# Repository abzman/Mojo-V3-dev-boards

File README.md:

# Mojo-V3-dev-boards
boards to use my mojo v3 as a development system for other FPGA projects

5v levelshifter bard can be purchased from PCBway here: https://www.pcbway.com/project/shareproject/64_bit_bidirectional_5v_shield_for_mojoV3_945b0e26.html

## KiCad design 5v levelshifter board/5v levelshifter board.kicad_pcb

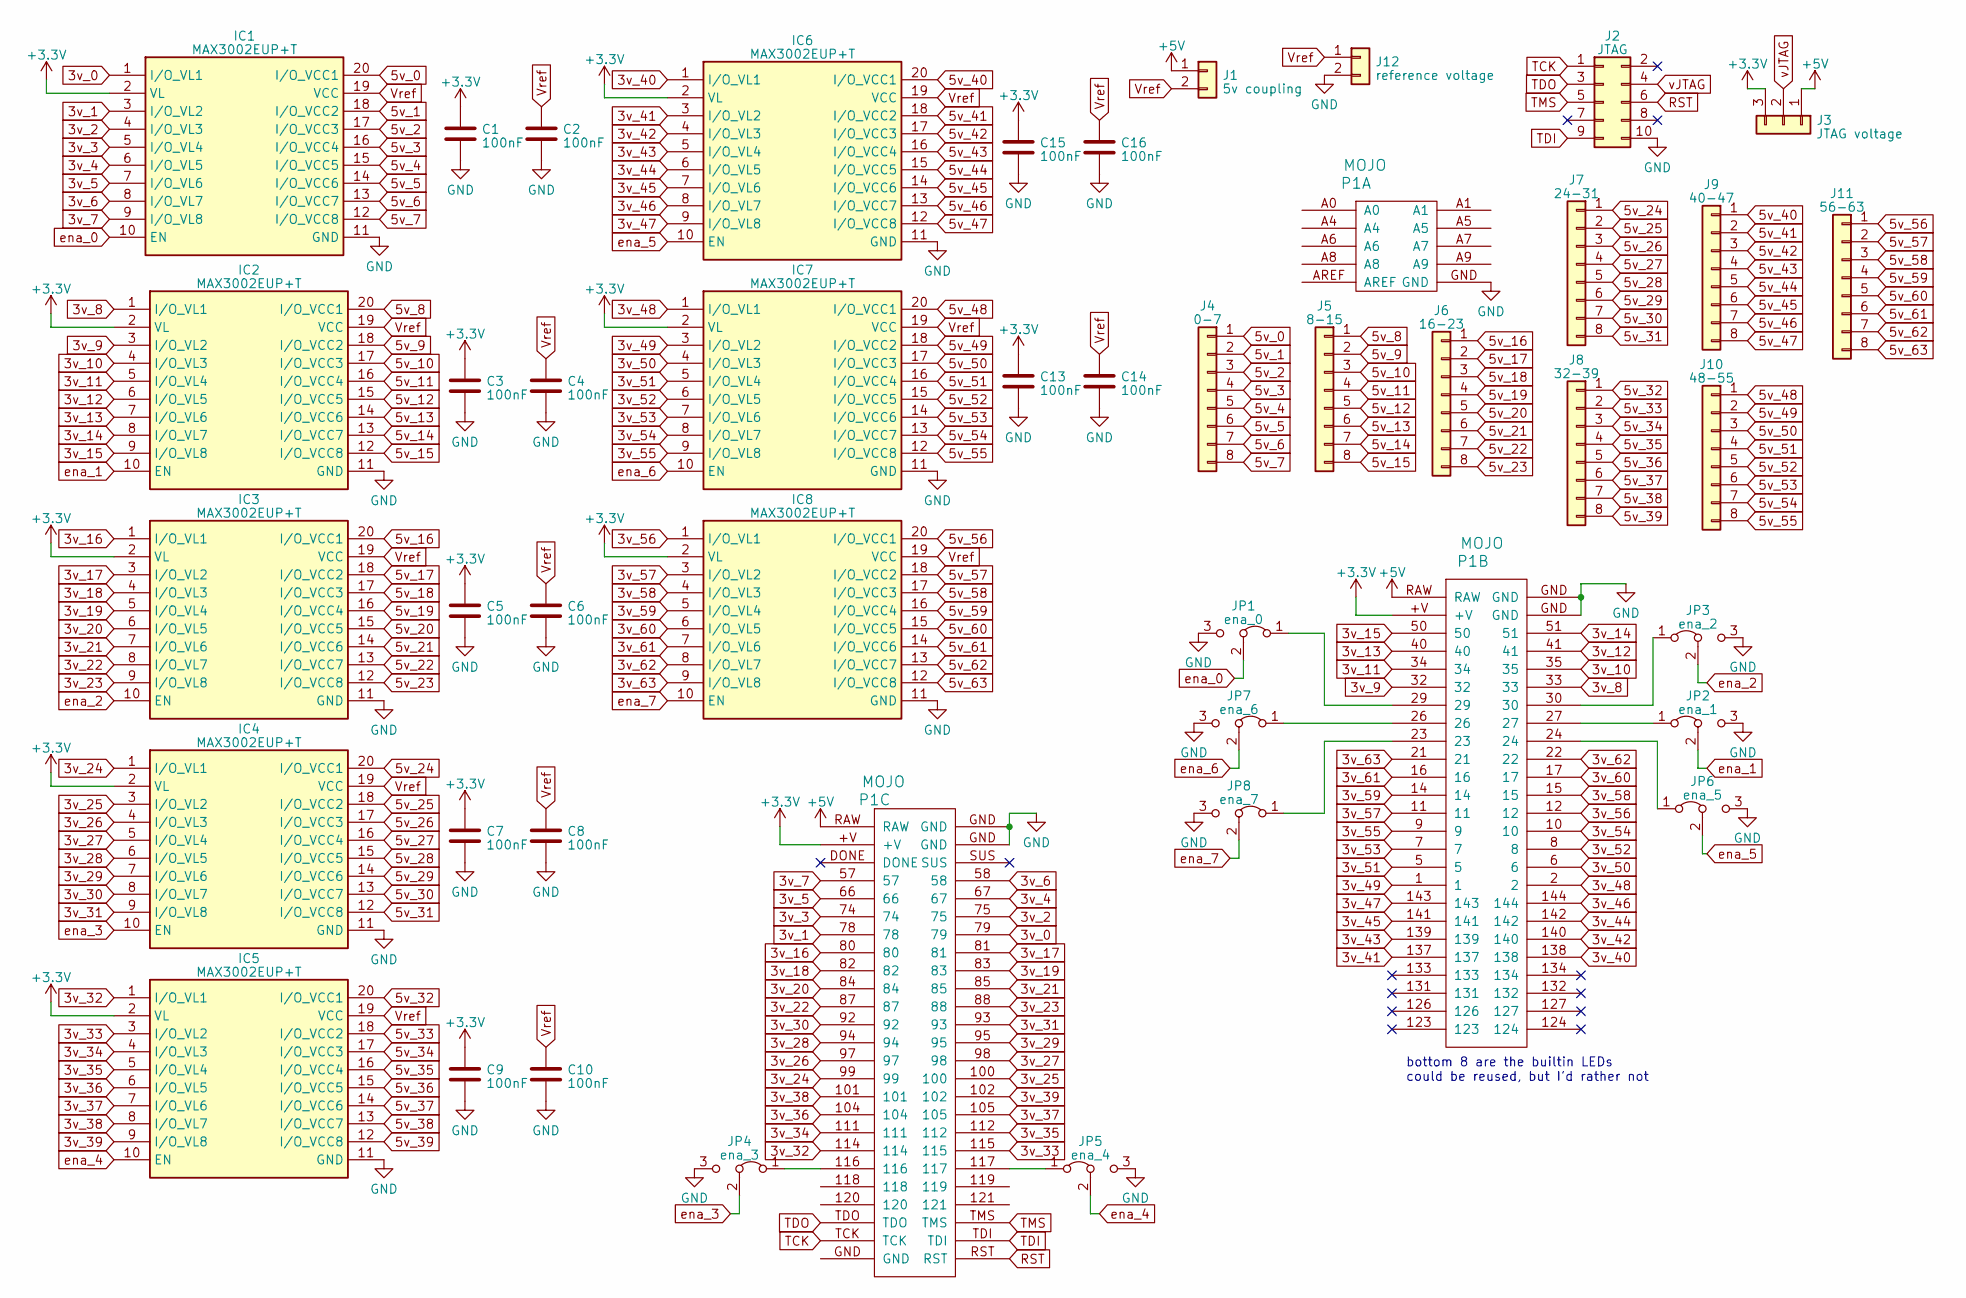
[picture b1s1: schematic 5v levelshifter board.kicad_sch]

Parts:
C1, C2, C3, C4, C5, C6, C7, C8, C9, C10, C13, C14, C15, C16: 100nF; C_0603_1608Metric
IC1, IC2, IC3, IC4, IC5, IC6, IC7, IC8: MAX3002EUP+T; SOP65P640X110-20N; Mouser Part Number 700-MAX3002EUPT
J1: 5v coupling; PinHeader_2x01_P2.54mm_Vertical
J2: JTAG; PinHeader_2x05_P2.54mm_Vertical
J3: JTAG voltage; PinHeader_1x03_P2.54mm_Vertical
J4: 0-7; PinHeader_1x08_P2.54mm_Vertical
J5: 8-15; PinHeader_1x08_P2.54mm_Vertical
J6: 16-23; PinHeader_1x08_P2.54mm_Vertical
J7: 24-31; PinHeader_1x08_P2.54mm_Vertical
J8: 32-39; PinHeader_1x08_P2.54mm_Vertical
J9: 40-47; PinHeader_1x08_P2.54mm_Vertical
J10: 48-55; PinHeader_1x08_P2.54mm_Vertical
J11: 56-63; PinHeader_1x08_P2.54mm_Vertical
J12: reference voltage; PinHeader_2x01_P2.54mm_Vertical
JP1: ena_0; SolderJumper-3_P1.3mm_Bridged12_RoundedPad1.0x1.5mm_NumberL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
JP2: ena_1; SolderJumper-3_P1.3mm_Bridged12_RoundedPad1.0x1.5mm_NumberL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
JP3: ena_2; SolderJumper-3_P1.3mm_Bridged12_RoundedPad1.0x1.5mm_NumberL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
JP4: ena_3; SolderJumper-3_P1.3mm_Bridged12_RoundedPad1.0x1.5mm_NumberL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
JP5: ena_4; SolderJumper-3_P1.3mm_Bridged12_RoundedPad1.0x1.5mm_NumberL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
JP6: ena_5; SolderJumper-3_P1.3mm_Bridged12_RoundedPad1.0x1.5mm_NumberL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
JP7: ena_6; SolderJumper-3_P1.3mm_Bridged12_RoundedPad1.0x1.5mm_NumberL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
JP8: ena_7; SolderJumper-3_P1.3mm_Bridged12_RoundedPad1.0x1.5mm_NumberL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
P1: MOJO; Mojo

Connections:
3v_0: IC1.1 (I/O_VL1), P1.79
3v_1: IC1.3 (I/O_VL2), P1.78
3v_2: IC1.4 (I/O_VL3), P1.75
3v_3: IC1.5 (I/O_VL4), P1.74
3v_4: IC1.6 (I/O_VL5), P1.67
3v_5: IC1.7 (I/O_VL6), P1.66
3v_6: IC1.8 (I/O_VL7), P1.58
3v_7: IC1.9 (I/O_VL8), P1.57
3v_8: IC2.1 (I/O_VL1), P1.33
3v_9: IC2.3 (I/O_VL2), P1.32
3v_10: IC2.4 (I/O_VL3), P1.35
3v_11: IC2.5 (I/O_VL4), P1.34
3v_12: IC2.6 (I/O_VL5), P1.41
3v_13: IC2.7 (I/O_VL6), P1.40
3v_14: IC2.8 (I/O_VL7), P1.51
3v_15: IC2.9 (I/O_VL8), P1.50
3v_16: IC3.1 (I/O_VL1), P1.80
3v_17: IC3.3 (I/O_VL2), P1.81
3v_18: IC3.4 (I/O_VL3), P1.82
3v_19: IC3.5 (I/O_VL4), P1.83
3v_20: IC3.6 (I/O_VL5), P1.84
3v_21: IC3.7 (I/O_VL6), P1.85
3v_22: IC3.8 (I/O_VL7), P1.87
3v_23: IC3.9 (I/O_VL8), P1.88
3v_24: IC4.1 (I/O_VL1), P1.99
3v_25: IC4.3 (I/O_VL2), P1.100
3v_26: IC4.4 (I/O_VL3), P1.97
3v_27: IC4.5 (I/O_VL4), P1.98
3v_28: IC4.6 (I/O_VL5), P1.94
3v_29: IC4.7 (I/O_VL6), P1.95
3v_30: IC4.8 (I/O_VL7), P1.92
3v_31: IC4.9 (I/O_VL8), P1.93
3v_32: IC5.1 (I/O_VL1), P1.114
3v_33: IC5.3 (I/O_VL2), P1.115
3v_34: IC5.4 (I/O_VL3), P1.111
3v_35: IC5.5 (I/O_VL4), P1.112
3v_36: IC5.6 (I/O_VL5), P1.104
3v_37: IC5.7 (I/O_VL6), P1.105
3v_38: IC5.8 (I/O_VL7), P1.101
3v_39: IC5.9 (I/O_VL8), P1.102
3v_40: IC6.1 (I/O_VL1), P1.138
3v_41: IC6.3 (I/O_VL2), P1.137
3v_42: IC6.4 (I/O_VL3), P1.140
3v_43: IC6.5 (I/O_VL4), P1.139
3v_44: IC6.6 (I/O_VL5), P1.142
3v_45: IC6.7 (I/O_VL6), P1.141
3v_46: IC6.8 (I/O_VL7), P1.144
3v_47: IC6.9 (I/O_VL8), P1.143
3v_48: IC7.1 (I/O_VL1), P1.2
3v_49: IC7.3 (I/O_VL2), P1.1
3v_50: IC7.4 (I/O_VL3), P1.6
3v_51: IC7.5 (I/O_VL4), P1.5
3v_52: IC7.6 (I/O_VL5), P1.8
3v_53: IC7.7 (I/O_VL6), P1.7
3v_54: IC7.8 (I/O_VL7), P1.10
3v_55: IC7.9 (I/O_VL8), P1.9
3v_56: IC8.1 (I/O_VL1), P1.12
3v_57: IC8.3 (I/O_VL2), P1.11
3v_58: IC8.4 (I/O_VL3), P1.15
3v_59: IC8.5 (I/O_VL4), P1.14
3v_60: IC8.6 (I/O_VL5), P1.17
3v_61: IC8.7 (I/O_VL6), P1.16
3v_62: IC8.8 (I/O_VL7), P1.22
3v_63: IC8.9 (I/O_VL8), P1.21
5v_0: IC1.20 (I/O_VCC1), J4.1
5v_1: IC1.18 (I/O_VCC2), J4.2
5v_2: IC1.17 (I/O_VCC3), J4.3
5v_3: IC1.16 (I/O_VCC4), J4.4
5v_4: IC1.15 (I/O_VCC5), J4.5
5v_5: IC1.14 (I/O_VCC6), J4.6
5v_6: IC1.13 (I/O_VCC7), J4.7
5v_7: IC1.12 (I/O_VCC8), J4.8
5v_8: IC2.20 (I/O_VCC1), J5.1
5v_9: IC2.18 (I/O_VCC2), J5.2
5v_10: IC2.17 (I/O_VCC3), J5.3
5v_11: IC2.16 (I/O_VCC4), J5.4
5v_12: IC2.15 (I/O_VCC5), J5.5
5v_13: IC2.14 (I/O_VCC6), J5.6
5v_14: IC2.13 (I/O_VCC7), J5.7
5v_15: IC2.12 (I/O_VCC8), J5.8
5v_16: IC3.20 (I/O_VCC1), J6.1
5v_17: IC3.18 (I/O_VCC2), J6.2
5v_18: IC3.17 (I/O_VCC3), J6.3
5v_19: IC3.16 (I/O_VCC4), J6.4
5v_20: IC3.15 (I/O_VCC5), J6.5
5v_21: IC3.14 (I/O_VCC6), J6.6
5v_22: IC3.13 (I/O_VCC7), J6.7
5v_23: IC3.12 (I/O_VCC8), J6.8
5v_24: IC4.20 (I/O_VCC1), J7.1
5v_25: IC4.18 (I/O_VCC2), J7.2
5v_26: IC4.17 (I/O_VCC3), J7.3
5v_27: IC4.16 (I/O_VCC4), J7.4
5v_28: IC4.15 (I/O_VCC5), J7.5
5v_29: IC4.14 (I/O_VCC6), J7.6
5v_30: IC4.13 (I/O_VCC7), J7.7
5v_31: IC4.12 (I/O_VCC8), J7.8
5v_32: IC5.20 (I/O_VCC1), J8.1
5v_33: IC5.18 (I/O_VCC2), J8.2
5v_34: IC5.17 (I/O_VCC3), J8.3
5v_35: IC5.16 (I/O_VCC4), J8.4
5v_36: IC5.15 (I/O_VCC5), J8.5
5v_37: IC5.14 (I/O_VCC6), J8.6
5v_38: IC5.13 (I/O_VCC7), J8.7
5v_39: IC5.12 (I/O_VCC8), J8.8
5v_40: IC6.20 (I/O_VCC1), J9.1
5v_41: IC6.18 (I/O_VCC2), J9.2
5v_42: IC6.17 (I/O_VCC3), J9.3
5v_43: IC6.16 (I/O_VCC4), J9.4
5v_44: IC6.15 (I/O_VCC5), J9.5
5v_45: IC6.14 (I/O_VCC6), J9.6
5v_46: IC6.13 (I/O_VCC7), J9.7
5v_47: IC6.12 (I/O_VCC8), J9.8
5v_48: IC7.20 (I/O_VCC1), J10.1
5v_49: IC7.18 (I/O_VCC2), J10.2
5v_50: IC7.17 (I/O_VCC3), J10.3
5v_51: IC7.16 (I/O_VCC4), J10.4
5v_52: IC7.15 (I/O_VCC5), J10.5
5v_53: IC7.14 (I/O_VCC6), J10.6
5v_54: IC7.13 (I/O_VCC7), J10.7
5v_55: IC7.12 (I/O_VCC8), J10.8
5v_56: IC8.20 (I/O_VCC1), J11.1
5v_57: IC8.18 (I/O_VCC2), J11.2
5v_58: IC8.17 (I/O_VCC3), J11.3
5v_59: IC8.16 (I/O_VCC4), J11.4
5v_60: IC8.15 (I/O_VCC5), J11.5
5v_61: IC8.14 (I/O_VCC6), J11.6
5v_62: IC8.13 (I/O_VCC7), J11.7
5v_63: IC8.12 (I/O_VCC8), J11.8
+3.3V: C1.1, C3.1, C5.1, C7.1, C9.1, C13.1, C15.1, IC1.2 (VL), IC2.2 (VL), IC3.2 (VL), IC4.2 (VL), IC5.2 (VL), IC6.2 (VL), IC7.2 (VL), IC8.2 (VL), J3.3, P1.+V
+5V: J1.1, J3.1, P1.RAW
GND: C1.2, C2.2, C3.2, C4.2, C5.2, C6.2, C7.2, C8.2, C9.2, C10.2, C13.2, C14.2, C15.2, C16.2, IC1.11 (GND), IC2.11 (GND), IC3.11 (GND), IC4.11 (GND), IC5.11 (GND), IC6.11 (GND), IC7.11 (GND), IC8.11 (GND), J2.10, J12.2, JP1.3 (B), JP2.3 (B), JP3.3 (B), JP4.3 (B), JP5.3 (B), JP6.3 (B), JP7.3 (B), JP8.3 (B), P1.GND
unnamed: JP1.1 (A), P1.29
unnamed: JP2.1 (A), P1.27
unnamed: JP3.1 (A), P1.30
unnamed: JP4.1 (A), P1.116
unnamed: JP5.1 (A), P1.117
unnamed: JP6.1 (A), P1.24
unnamed: JP7.1 (A), P1.26
unnamed: JP8.1 (A), P1.23
RST: J2.6, P1.RST
TCK: J2.1, P1.TCK
TDI: J2.9, P1.TDI
TDO: J2.3, P1.TDO
TMS: J2.5, P1.TMS
Vref: C2.1, C4.1, C6.1, C8.1, C10.1, C14.1, C16.1, IC1.19 (VCC), IC2.19 (VCC), IC3.19 (VCC), IC4.19 (VCC), IC5.19 (VCC), IC6.19 (VCC), IC7.19 (VCC), IC8.19 (VCC), J1.2, J12.1
ena_0: IC1.10 (EN), JP1.2 (C)
ena_1: IC2.10 (EN), JP2.2 (C)
ena_2: IC3.10 (EN), JP3.2 (C)
ena_3: IC4.10 (EN), JP4.2 (C)
ena_4: IC5.10 (EN), JP5.2 (C)
ena_5: IC6.10 (EN), JP6.2 (C)
ena_6: IC7.10 (EN), JP7.2 (C)
ena_7: IC8.10 (EN), JP8.2 (C)
vJTAG: J2.4, J3.2

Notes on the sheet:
bottom 8 are the builtin LEDs could be reused, but I'd rather not

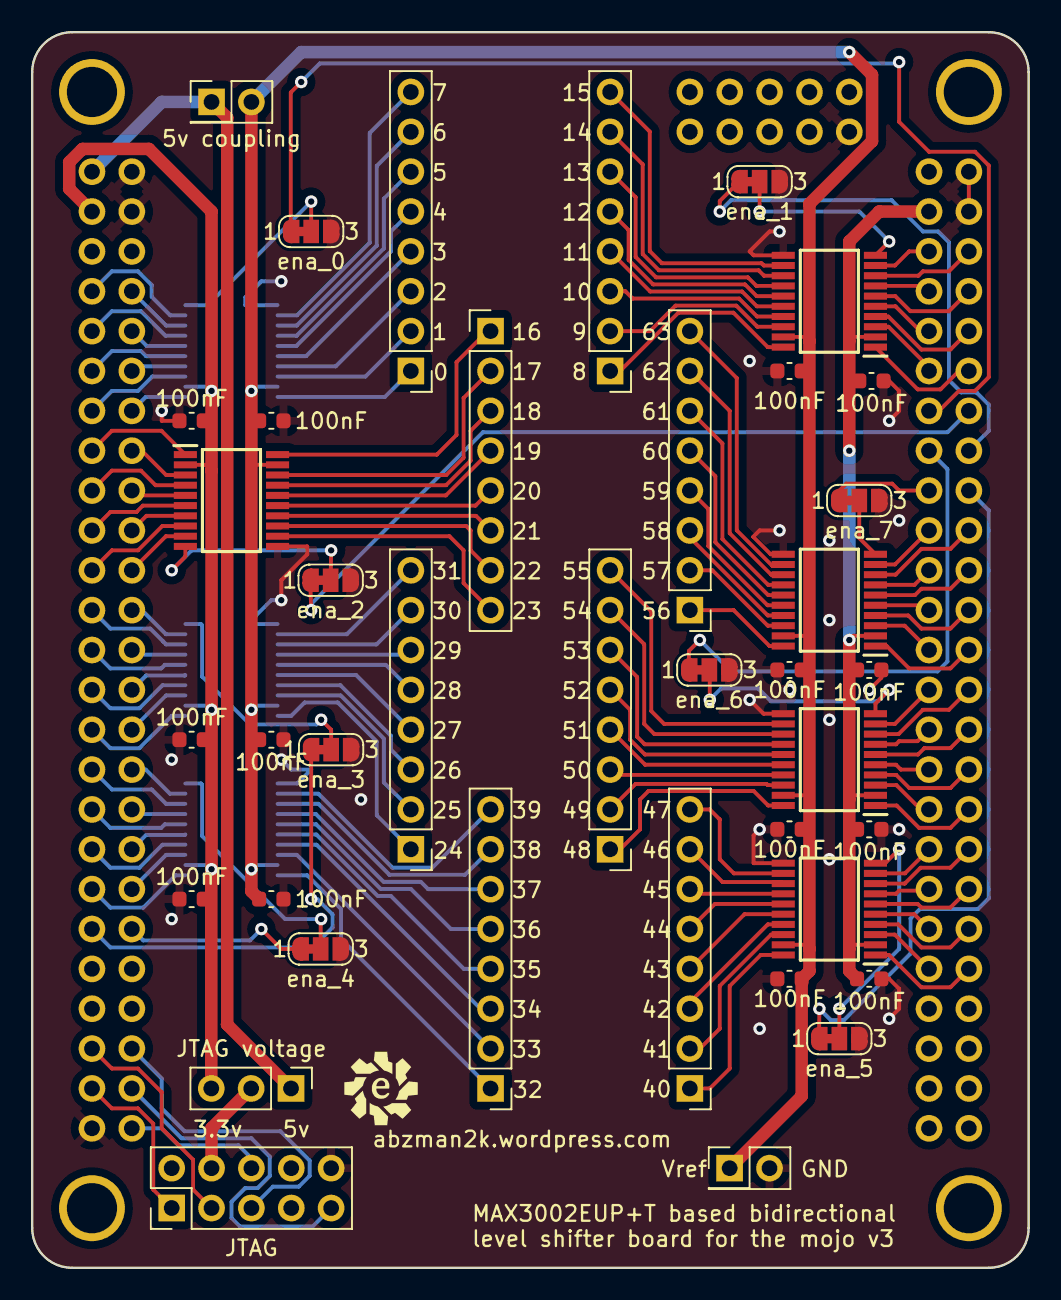
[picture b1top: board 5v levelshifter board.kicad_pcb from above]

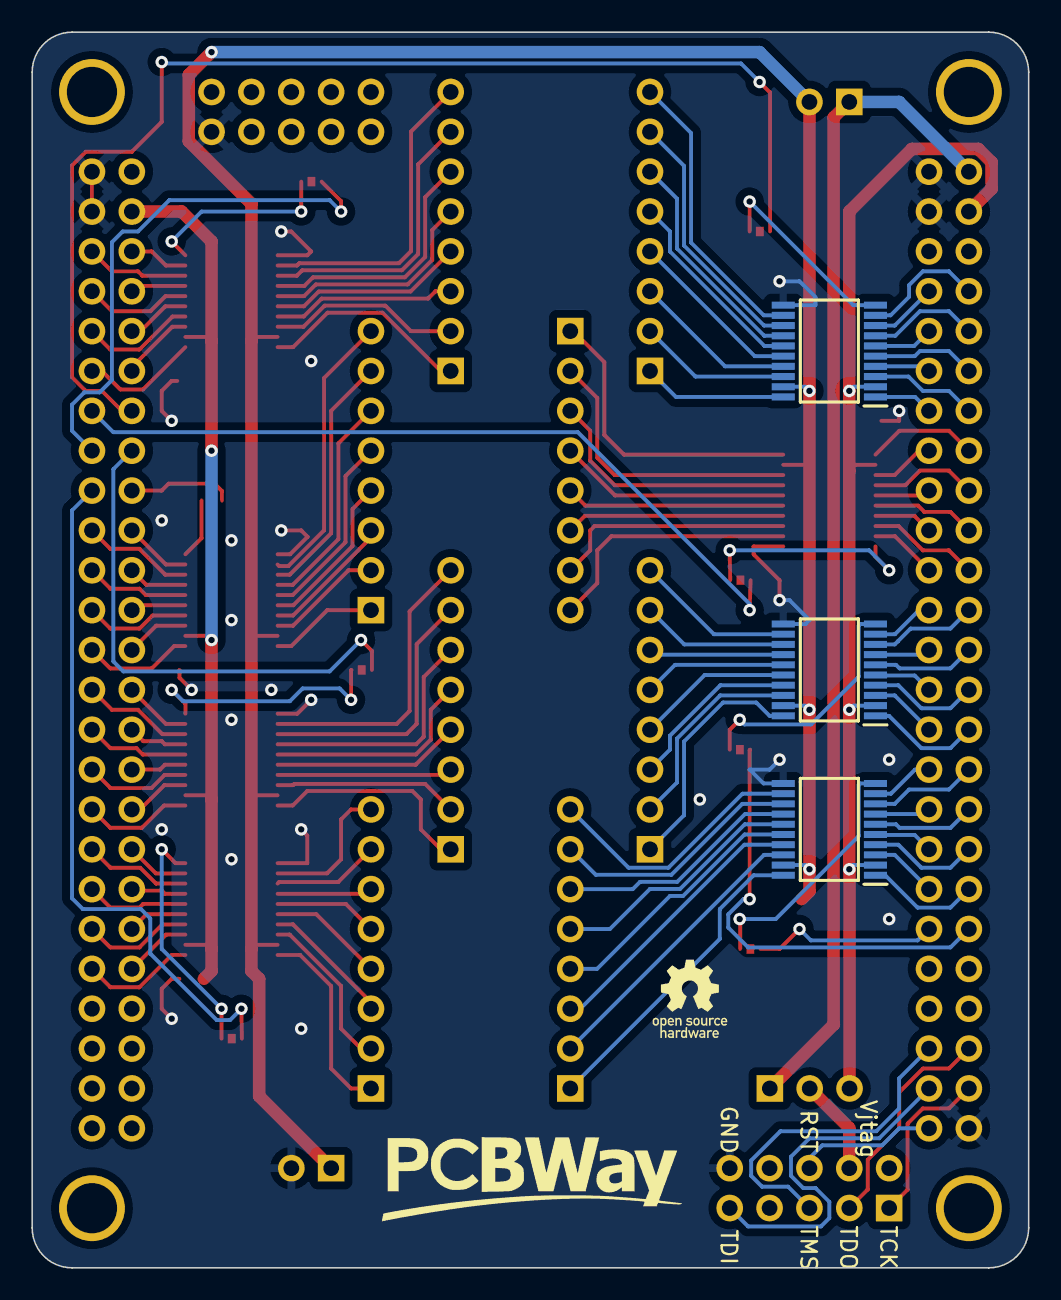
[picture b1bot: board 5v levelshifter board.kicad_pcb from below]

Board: 2 copper layers, 63.5 x 78.7 mm, 43 parts (3 on the bottom side), 154 nets.

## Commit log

2023-04-19 designed board that's a superset of the servo shield
2023-04-19 revised gitignore
2023-06-06 revised board design and added gerber files
2023-06-06 base project with ucf for this shield
2023-06-06 added code to sample 8 bits of data on the rising edge of one trigger pin and print them to serial as a set of hex digits
2023-06-06 code for testing 7404 inverters in-circuit
2023-06-06 added BOM
2023-06-06 Update README.md
    added link to PCBway for purchase
